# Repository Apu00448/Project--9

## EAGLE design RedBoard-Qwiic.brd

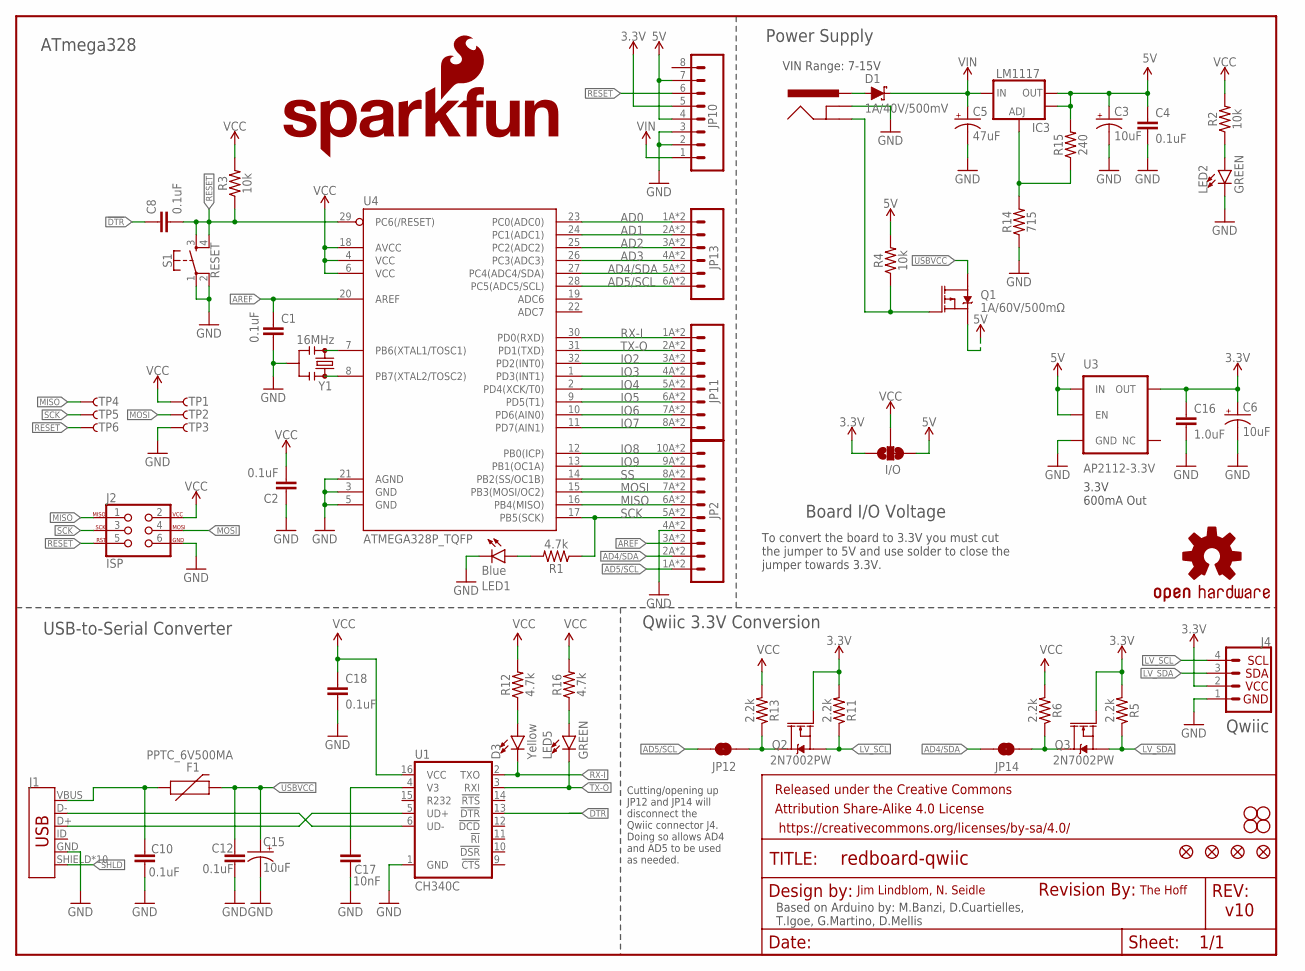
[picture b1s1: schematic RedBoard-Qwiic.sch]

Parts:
C1, C2, C4, C8, C10, C12, C18: 0.1uF; 0603
C3, C6, C15: 10uF; EIA3216
C5: 47uF; PANASONIC_D
C16: 1.0uF; 0603-CAP
C17: 10nF; 0603-CAP
D1: 1A/40V/500mV; SMA-DIODE
D3: Yellow; LED-1206-HIDDENSILK
F1: PPTC_6V500MA; 0805
FRAME2: FRAME-LETTER; CREATIVE_COMMONS
I/O: JUMPER-SMT_3_1-NC_TRACE_SILK; SMT-JUMPER_3_1-NC_TRACE_SILK
IC3: LM1117; SOT223-ALT1
J1: AMP FCI 10103594-0001LF; USB-MICROB-PTH-MILL
J2: ISP; 2X3_SMT_POSTS
J3: POWER_JACKSUPER_BOMB_DIGITY; POWER_JACK_SMD_OVERPASTE_SUPER_BOMB_DIGITY
J4: QWIIC_CONNECTORJS-1MM; 1X04_1MM_RA
JP1: SFE_LOGO_NAME.1_INCH; SFE_LOGO_NAME_.1
JP2: M10SMD_COMBO; 1X10_SMD_COMBINED
JP3, JP4, JP5, JP6: STAND-OFF
JP7: SFE_LOGO_FLAME.1_INCH; SFE_LOGO_FLAME_.1
JP8, JP9, JP15, JP16: FIDUCIAL1X2; FIDUCIAL-1X2
JP10: CONN_08SMD-COMBO-FEMALE; 1X08_SMD_COMBINED
JP11: JP11; 1X08_SMD_COMBINED@1
JP12, JP14: JUMPER-SMT_2_NC_TRACE_SILK; SMT-JUMPER_2_NC_TRACE_SILK
JP13: M06SMD-STRAIGHT-COMBO; 1X06_SMD_STRAIGHT_COMBO
LED1: Blue; LED-1206-HIDDENSILK
LED2, LED5: GREEN; LED-1206-HIDDENSILK
LOGO1: REVISION
Q1: 1A/60V/500mΩ; SOT23-3
Q2, Q3: 2N7002PW; SOT323
R1, R12, R16: 4.7k; 0603
R2, R3, R4: 10k; 0603
R5, R6, R11, R13: 2.2k; 0603
R14: 715; 0603
R15: 240; 0603
S1: RESET; TACTILE_SWITCH_SMD_5.2MM
TP1, TP2, TP3, TP4, TP5, TP6: TP-3x5; PAD.03X.05
U1: CH340C; SO016
U3: AP2112-3.3V; SOT23-5
U4: ATMEGA328P_TQFP; TQFP32-08
U$16: OSHW-LOGOS; OSHW-LOGO-S
Y1: 16MHz; RESONATOR-SMD-3.2X1.3

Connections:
3.3V: C6.+, C16.1, I/O.1, J4.2, JP10.5, Q2.1 (G), Q3.1 (G), R5.2, R11.2, U3.5 (OUT)
5V: C3.+, C4.1, I/O.3, IC3.2 (OUT), IC3.4 (OUT), JP10.4, JP10.7, Q1.2 (S), R4.2, R15.2, U3.1 (IN), U3.3 (EN)
!DTR: C8.1, U1.13 (!DTR)
AD0: JP13.1A (1), JP13.1B (1), U4.23 (PC0(ADC0))
AD1: JP13.2A (2), JP13.2B (2), U4.24 (PC1(ADC1))
AD2: JP13.3A (3), JP13.3B (3), U4.25 (PC2(ADC2))
AD3: JP13.4A (4), JP13.4B (4), U4.26 (PC3(ADC3))
AD4/SDA: JP2.2A (2), JP2.2B (2), JP13.5A (5), JP13.5B (5), JP14.2, U4.27 (PC4(ADC4/SDA))
AD5/SCL: JP2.1A (1), JP2.1B (1), JP12.2, JP13.6A (6), JP13.6B (6), U4.28 (PC5(ADC5/SCL))
AREF: C1.1, JP2.3A (3), JP2.3B (3), U4.20 (AREF)
GND: C1.2, C2.1, C3.-, C4.2, C5.-, C6.-, C10.2, C12.2, C15.-, C16.2, C17.2, C18.2, J1.GND, J2.6, J3.GND (GNDBREAK), J4.1, JP2.4A (4), JP2.4B (4), JP10.2, JP10.3, LED1.C, LED2.C, R14.1, S1.1, S1.2, TP3.P$1, U1.1 (GND), U3.2 (GND), U4.3 (GND), U4.5 (GND), U4.21 (AGND), Y1.2
INSERT: J3.P$4 (GND), Q1.1 (G), R4.1
IO2: JP11.3A (3), JP11.3B (3), U4.32 (PD2(INT0))
IO3: JP11.4A (4), JP11.4B (4), U4.1 (PD3(INT1))
IO4: JP11.5A (5), JP11.5B (5), U4.2 (PD4(XCK/T0))
IO5: JP11.6A (6), JP11.6B (6), U4.9 (PD5(T1))
IO6: JP11.7A (7), JP11.7B (7), U4.10 (PD6(AIN0))
IO7: JP11.8A (8), JP11.8B (8), U4.11 (PD7(AIN1))
IO8: JP2.10A (10), JP2.10B (10), U4.12 (PB0(ICP))
IO9: JP2.9A (9), JP2.9B (9), U4.13 (PB1(OC1A))
LV_SCL: J4.4, Q2.2 (S), R11.1
LV_SDA: J4.3, Q3.2 (S), R5.1
MISO: J2.1, JP2.6A (6), JP2.6B (6), TP4.P$1, U4.16 (PB4(MISO))
MOSI: J2.4, JP2.7A (7), JP2.7B (7), TP2.P$1, U4.15 (PB3(MOSI/OC2))
unnamed: LED1.A, R1.2
unnamed: LED2.A, R2.1
unnamed: U4.7 (PB6(XTAL1/TOSC1)), Y1.1
unnamed: U4.8 (PB7(XTAL2/TOSC2)), Y1.3
unnamed: LED5.A, R16.1
unnamed: C17.1, U1.4 (V3)
unnamed: JP12.1, Q2.3 (D), R13.1
unnamed: JP14.1, Q3.3 (D), R6.1
unnamed: D3.A, R12.1
unnamed: J1.D-, U1.6 (UD-)
unnamed: J1.D+, U1.5 (UD+)
unnamed: IC3.1 (ADJ), R14.2, R15.1
PWRIN: D1.A, J3.VIN0 (PWR)
RESET: C8.2, J2.5, JP10.6, R3.1, S1.3, S1.4, TP6.P$1, U4.29 (PC6(/RESET))
RX-I: D3.C, JP11.1A (1), JP11.1B (1), U1.2 (TXO), U4.30 (PD0(RXD))
SCK: J2.3, JP2.5A (5), JP2.5B (5), R1.1, TP5.P$1, U4.17 (PB5(SCK))
SHLD: J1.SHIELD, J1.SHIELD2 (SHIELD), J1.SHIELD3 (SHIELD), J1.SHIELD4 (SHIELD), J1.SHIELD5 (SHIELD), J1.SHIELD6 (SHIELD), J1.SHIELD7 (SHIELD), J1.SHIELD8 (SHIELD), J1.SHIELD9 (SHIELD), J1.SHIELD10 (SHIELD)
SS: JP2.8A (8), JP2.8B (8), U4.14 (PB2(SS/OC1B))
TX-O: JP11.2A (2), JP11.2B (2), LED5.C, U1.3 (RXI), U4.31 (PD1(TXD))
USBVCC: C12.1, C15.+, F1.2, Q1.3 (D)
VCC: C2.2, C18.1, I/O.2, J2.2, R2.2, R3.2, R6.2, R12.2, R13.2, R16.2, TP1.P$1, U1.16 (VCC), U4.4 (VCC), U4.6 (VCC), U4.18 (AVCC)
VIN: C5.+, D1.C, IC3.3 (IN), JP10.1
VUSB: C10.1, F1.1, J1.VBUS

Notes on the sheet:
Power Supply
ATmega328
USB-to-Serial Converter
Based on Arduino by: M.Banzi, D.Cuartielles, T.Igoe, G.Martino, D.Mellis
Jim Lindblom, N. Seidle
v10
VIN Range: 7-15V
3.3V 600mA Out
Board I/O Voltage
To convert the board to 3.3V you must cut the jumper to 5V and use solder to close the jumper towards 3.3V.
Qwiic
Qwiic 3.3V Conversion
Cutting/opening up JP12 and JP14 will disconnect the Qwiic connector J4. Doing so allows AD4 and AD5 to be used as needed.
The Hoff

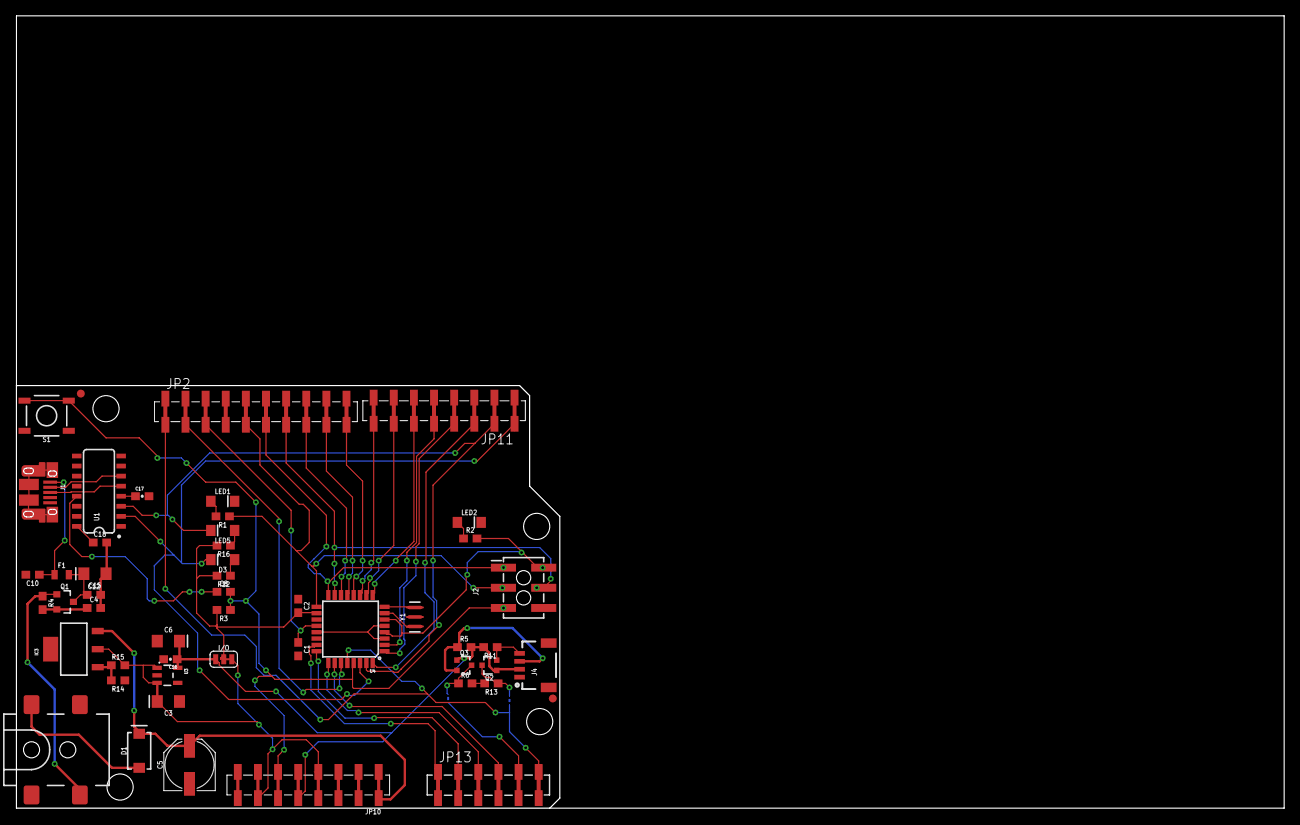
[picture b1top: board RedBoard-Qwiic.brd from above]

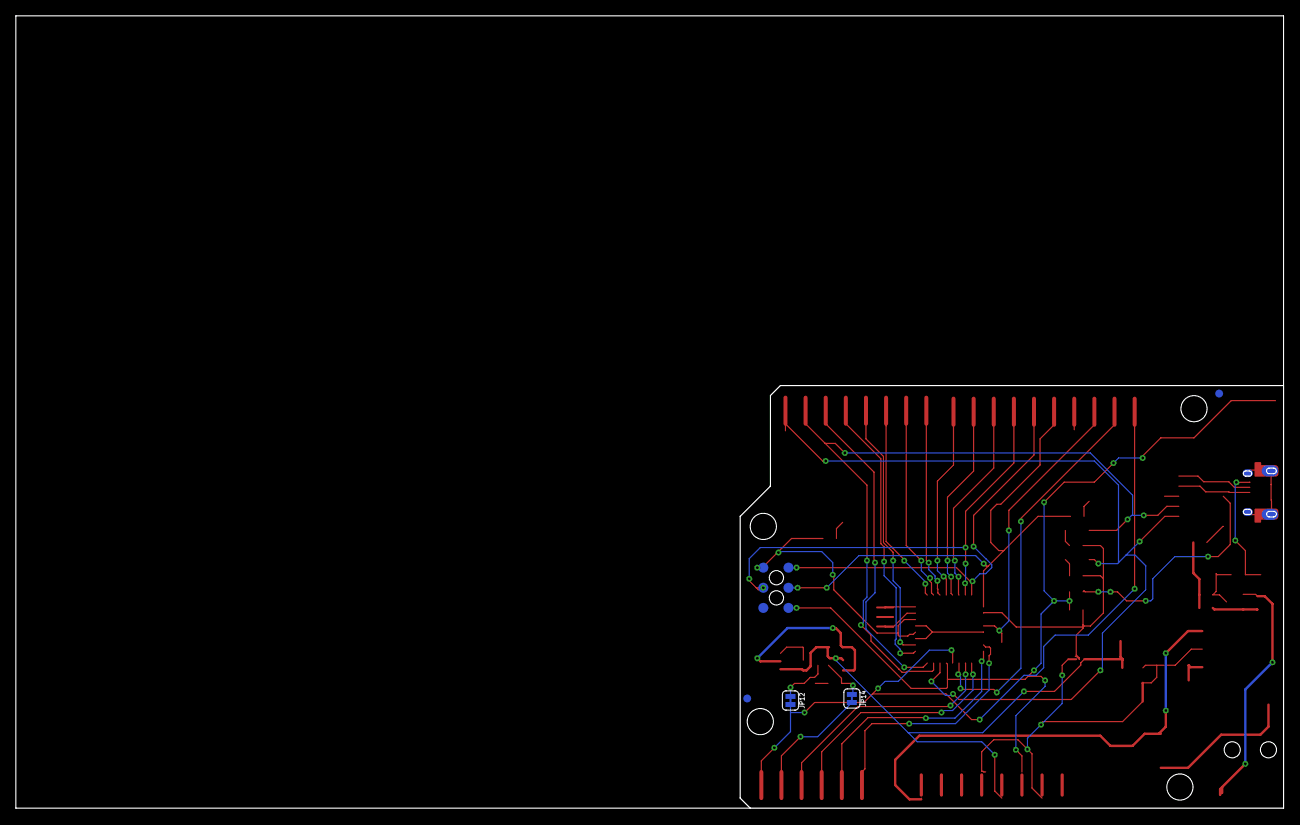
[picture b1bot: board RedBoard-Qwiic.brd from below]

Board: 2 copper layers, 160.0 x 100.0 mm, 70 parts (10 on the bottom side), 47 nets.

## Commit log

2024-01-03 Red Board- Eagle

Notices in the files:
parts and their libraries:
SparkFun-Capacitors: Licensing: CC v3.0 Share-Alike You are welcome to use this library for commercial purposes.
SparkFun-DiscreteSemi: Licensing: Creative Commons ShareAlike 4.0 International - https://creativecommons.org/licenses/by-sa/4.0
SparkFun-Aesthetics: Released under the Creative Commons
